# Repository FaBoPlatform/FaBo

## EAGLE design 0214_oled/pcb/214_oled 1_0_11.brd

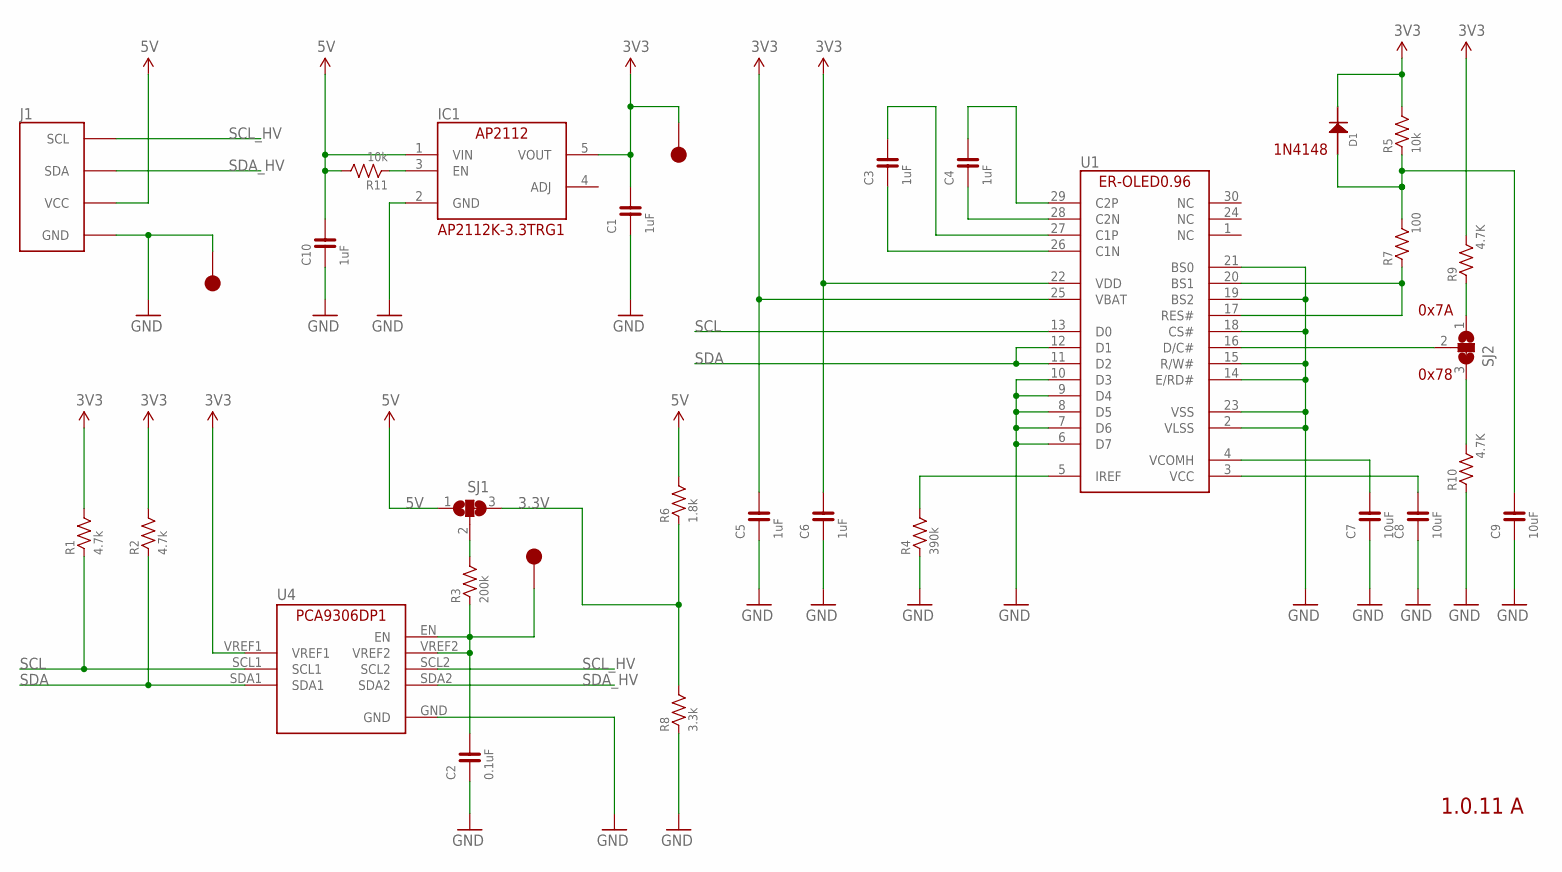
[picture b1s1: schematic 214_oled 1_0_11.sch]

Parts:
C1, C3, C4, C5, C6, C10: 1uF; 0603
C2: 0.1uF; 0603
C7, C8, C9: 10uF; 0603
D1: 1N4148; 1N4148W
IC1: AP2112K-3.3TRG1; SOT-23-5
J1: FABO_BRICK_I2C-OLED; FABO_BRICK_I2C_OLED
R1, R2: 4.7k; 0603
R3: 200k; 0603
R4: 390k; 0603
R5, R11: 10k; 0603
R6: 1.8k; 0603
R7: 100; 0603
R8: 3.3k; 0603
R9, R10: 4.7K; 0603
SJ1, SJ2: SJ2W; SJ_2
TP1, TP2, TP5: TP-15
U1: ER-OLED0.96-1ER-CON30HT-1; ER-CON30HT-1
U4: PCA9306DP1; TSSOP8

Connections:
3.3V: R6.1, R8.2, SJ1.3
3V3: C1.2, C5.2, C6.2, D1.CATHODE, IC1.5 (VOUT), R1.2, R2.2, R5.2, R9.2, TP5.1, U1.22 (VDD), U1.25 (VBAT), U4.VREF1
5V: C10.2, IC1.1 (VIN), J1.VCC, R6.2, R11.2, SJ1.1
GND: C1.1, C2.1, C5.1, C6.1, C7.1, C8.1, C9.1, C10.1, IC1.2 (GND), J1.GND, R4.1, R8.1, R10.1, TP1.1, U1.2 (VLSS), U1.6 (D7), U1.7 (D6), U1.8 (D5), U1.9 (D4), U1.10 (D3), U1.14 (E/RD#), U1.15 (R/W#), U1.18 (CS#), U1.19 (BS2), U1.21 (BS0), U1.23 (VSS), U4.GND
unnamed: C3.2, U1.27 (C1P)
unnamed: C3.1, U1.26 (C1N)
unnamed: C4.1, U1.28 (C2N)
unnamed: C4.2, U1.29 (C2P)
unnamed: R4.2, U1.5 (IREF)
unnamed: C7.2, U1.4 (VCOMH)
unnamed: C8.2, U1.3 (VCC)
unnamed: C2.2, R3.1, TP2.1, U4.EN, U4.VREF2
unnamed: R3.2, SJ1.2
unnamed: R7.1, U1.17 (RES#), U1.20 (BS1)
unnamed: IC1.3 (EN), R11.1
unnamed: C9.2, D1.ANODE, R5.1, R7.2
unnamed: SJ2.2, U1.16 (D/C#)
unnamed: R10.2, SJ2.3
unnamed: R9.1, SJ2.1
SCL: R1.1, U1.13 (D0), U4.SCL1
SCL_HV: J1.SCL, U4.SCL2
SDA: R2.1, U1.11 (D2), U1.12 (D1), U4.SDA1
SDA_HV: J1.SDA, U4.SDA2

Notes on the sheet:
1.0.11 A
1N4148
AP2112K-3.3TRG1
0x7A
0x78

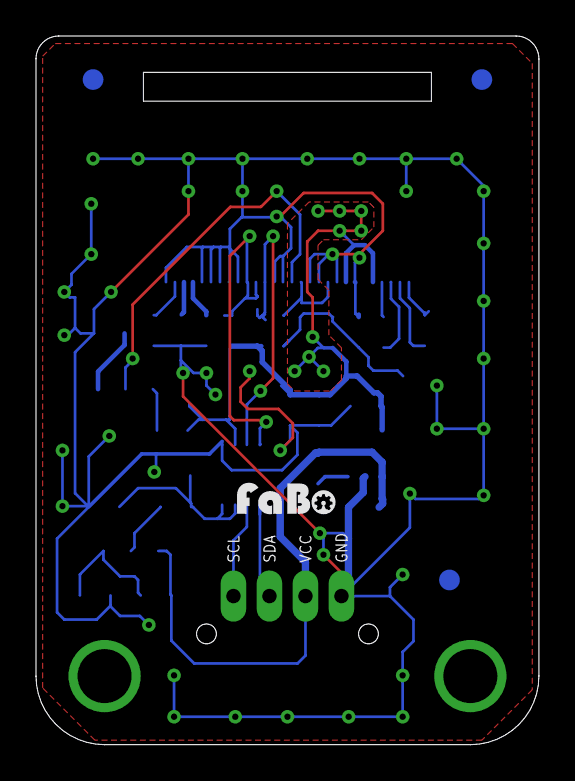
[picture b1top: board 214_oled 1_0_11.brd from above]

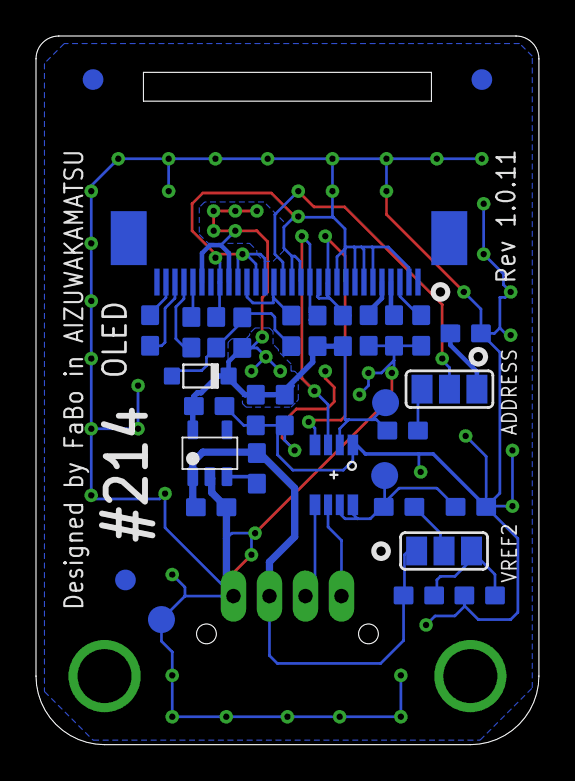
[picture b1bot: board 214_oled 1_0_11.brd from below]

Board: 2 copper layers, 27.9 x 39.4 mm, 35 parts (32 on the bottom side), 23 nets.

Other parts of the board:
U$3, U$4, U$5: MARK_POINT_3MM
U$6: LOGO_FABO_S

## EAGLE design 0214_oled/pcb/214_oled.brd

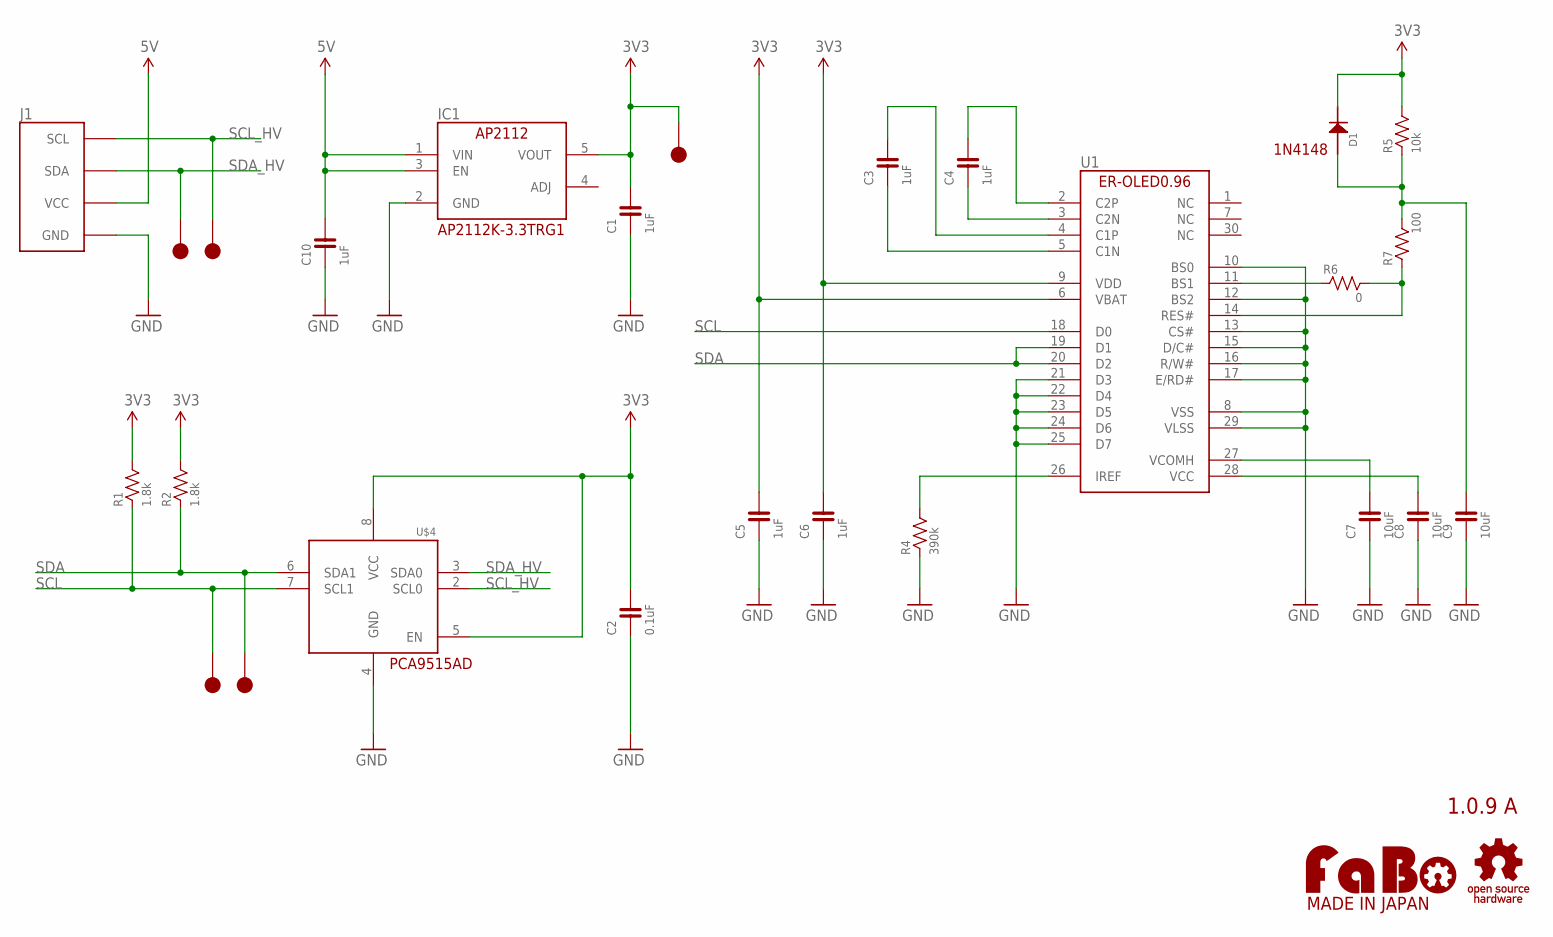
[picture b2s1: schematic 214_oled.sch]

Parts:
C1, C3, C4, C5, C6, C10: 1uF; 0603
C2: 0.1uF; 0603
C7, C8, C9: 10uF; 0603
D1: 1N4148; 1N4148W
IC1: AP2112K-3.3TRG1; SOT-23-5
J1: FABO_BRICK_I2C-OLED; FABO_BRICK_I2C_OLED
R1, R2: 1.8k; 0603
R4: 390k; 0603
R5: 10k; 0603
R6: 0; 0603
R7: 100; 0603
TP1, TP2, TP3, TP4, TP5: TP-15
U1: ER-OLED0.96-1
U$2: LOGO_OSHW-M; LOGO_OSHW_M
U$3: LOGO_FABO-M_BOTTOM; LOGO_FABO_MS_BOTTOM
U$4: PCA9515; SO8

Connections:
3V3: C1.2, C2.2, C5.2, C6.2, D1.CATHODE, IC1.5 (VOUT), R1.2, R2.2, R5.2, TP5.1, U1.6 (VBAT), U1.9 (VDD), U$4.5 (EN), U$4.8 (VCC)
5V: C10.2, IC1.1 (VIN), IC1.3 (EN), J1.VCC
GND: C1.1, C2.1, C5.1, C6.1, C7.1, C8.1, C9.1, C10.1, IC1.2 (GND), J1.GND, R4.1, U1.8 (VSS), U1.10 (BS0), U1.12 (BS2), U1.13 (CS#), U1.15 (D/C#), U1.16 (R/W#), U1.17 (E/RD#), U1.21 (D3), U1.22 (D4), U1.23 (D5), U1.24 (D6), U1.25 (D7), U1.29 (VLSS), U$4.4 (GND)
unnamed: C3.2, U1.4 (C1P)
unnamed: C3.1, U1.5 (C1N)
unnamed: C4.1, U1.3 (C2N)
unnamed: C4.2, U1.2 (C2P)
unnamed: R4.2, U1.26 (IREF)
unnamed: C7.2, U1.27 (VCOMH)
unnamed: C8.2, U1.28 (VCC)
unnamed: R6.1, U1.11 (BS1)
unnamed: R6.2, R7.1, U1.14 (RES#)
unnamed: C9.2, D1.ANODE, R5.1, R7.2
SCL: R1.1, TP2.1, U1.18 (D0), U$4.7 (SCL1)
SCL_HV: J1.SCL, TP4.1, U$4.2 (SCL0)
SDA: R2.1, TP1.1, U1.19 (D1), U1.20 (D2), U$4.6 (SDA1)
SDA_HV: J1.SDA, TP3.1, U$4.3 (SDA0)

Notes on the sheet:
1.0.9 A
1N4148
AP2112K-3.3TRG1
PCA9515AD

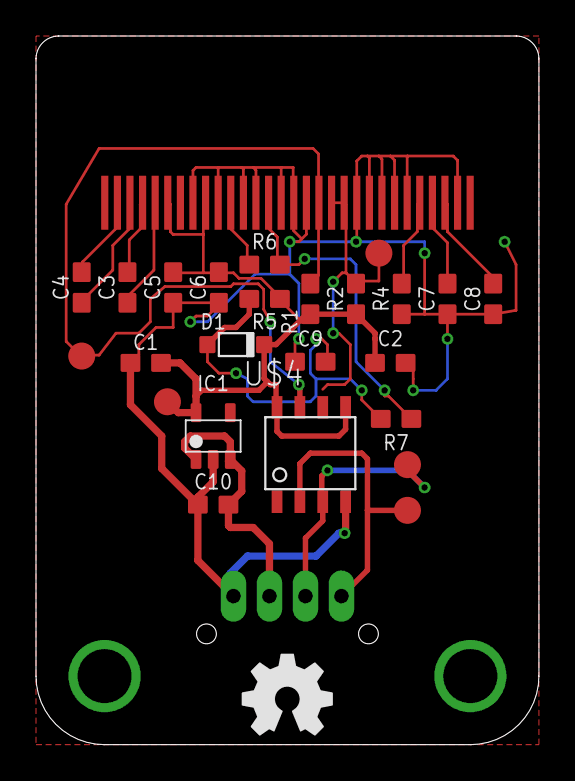
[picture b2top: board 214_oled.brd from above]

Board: 2 copper layers, 27.9 x 39.4 mm, 28 parts (1 on the bottom side), 17 nets.

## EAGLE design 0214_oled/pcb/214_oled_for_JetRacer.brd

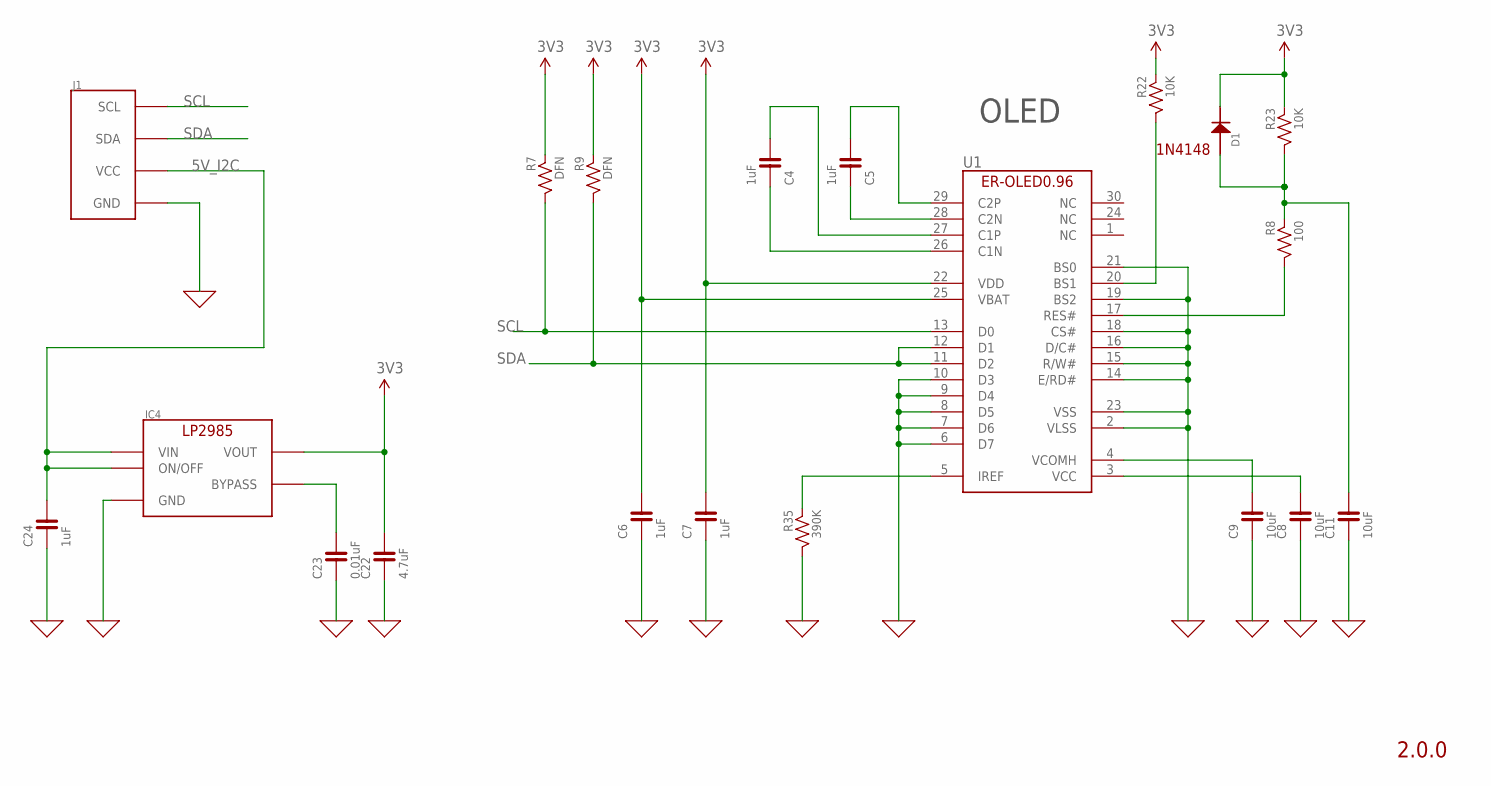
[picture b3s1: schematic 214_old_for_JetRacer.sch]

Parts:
C4, C5, C6, C7, C24: 1uF; 0603
C8, C9, C11: 10uF; 0603
C22: 4.7uF; 0603
C23: 0.01uF; 0603
D1: 1N4148; 1N4148W
IC4: LP2985-33DBV; SOT-23-5
J1: FABO_BRICK_I2C-S04B-PASK-2; FABO_BRICK_I2C_S04B-PASK-2
R7, R9: DFN; 0603
R8: 100; 0603
R22, R23: 10K; 0603
R35: 390K; 0603
U1: ER-OLED0.96-1ER-CON30HT-1; ER-CON30HT-1

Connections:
0: C6.1, C7.1, C8.1, C9.1, C11.1, C22.1, C23.1, C24.1, IC4.2 (GND), J1.GND, R35.2, U1.2 (VLSS), U1.6 (D7), U1.7 (D6), U1.8 (D5), U1.9 (D4), U1.10 (D3), U1.14 (E/RD#), U1.15 (R/W#), U1.16 (D/C#), U1.18 (CS#), U1.19 (BS2), U1.21 (BS0), U1.23 (VSS)
3V3: C6.2, C7.2, C22.2, D1.CATHODE, IC4.5 (VOUT), R7.1, R9.1, R22.1, R23.1, U1.22 (VDD), U1.25 (VBAT)
5V_I2C: C24.2, IC4.1 (VIN), IC4.3 (ON/OFF), J1.VCC
unnamed: C23.2, IC4.4 (BYPASS)
unnamed: C4.2, U1.27 (C1P)
unnamed: C4.1, U1.26 (C1N)
unnamed: C5.1, U1.28 (C2N)
unnamed: C5.2, U1.29 (C2P)
unnamed: R35.1, U1.5 (IREF)
unnamed: C9.2, U1.4 (VCOMH)
unnamed: C8.2, U1.3 (VCC)
unnamed: R8.2, U1.17 (RES#)
unnamed: C11.2, D1.ANODE, R8.1, R23.2
unnamed: R22.2, U1.20 (BS1)
SCL: J1.SCL, R7.2, U1.13 (D0)
SDA: J1.SDA, R9.2, U1.11 (D2), U1.12 (D1)

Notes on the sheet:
1N4148
OLED
2.0.0

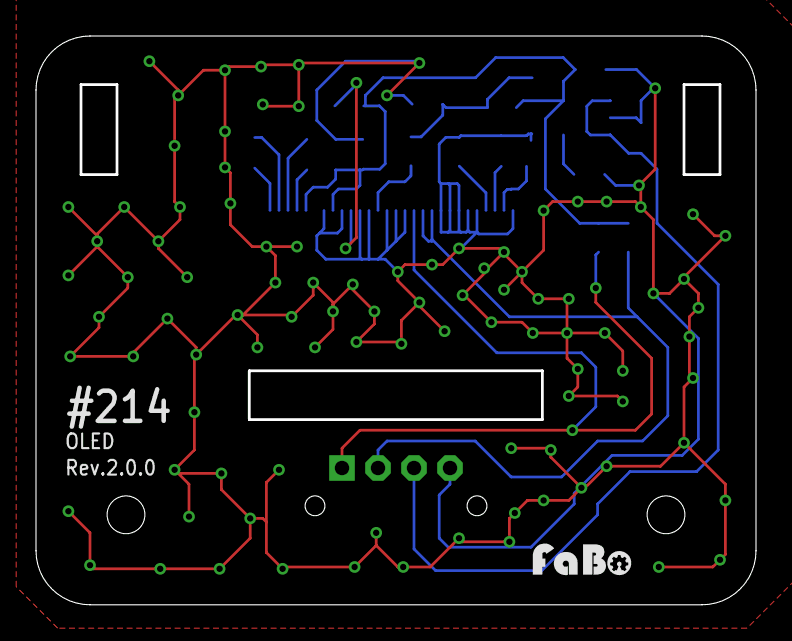
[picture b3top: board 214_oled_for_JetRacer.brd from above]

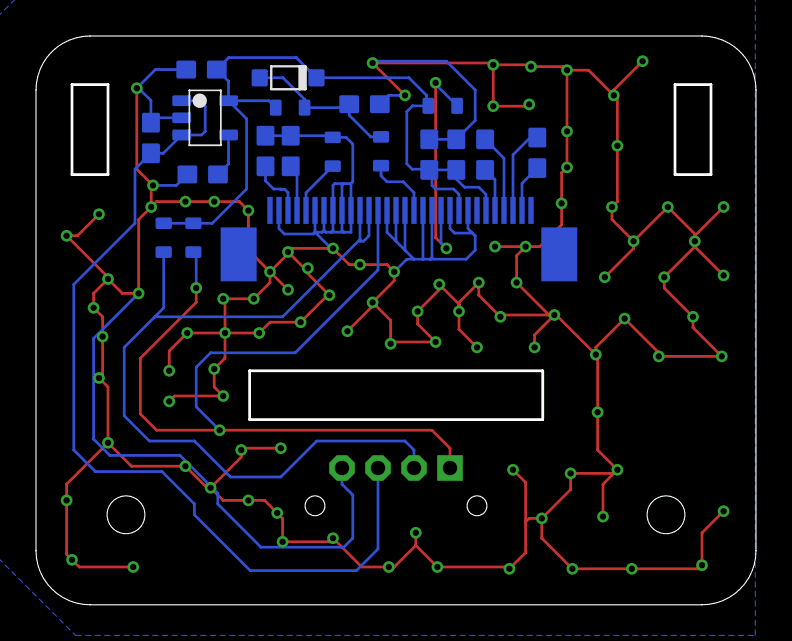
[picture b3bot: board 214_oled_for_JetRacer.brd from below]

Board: 2 copper layers, 40.0 x 31.6 mm, 21 parts (18 on the bottom side), 16 nets.

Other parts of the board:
U$1: LOGO_FABO_S

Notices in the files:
parts and their libraries:
FaBo-Symbol: Released under the Creative Commons Attribution-ShareAlike 4.0 License
https://creativecommons.org/licenses/by-sa/4.0
FaBo-Symbol: Released under the Creative Commons
